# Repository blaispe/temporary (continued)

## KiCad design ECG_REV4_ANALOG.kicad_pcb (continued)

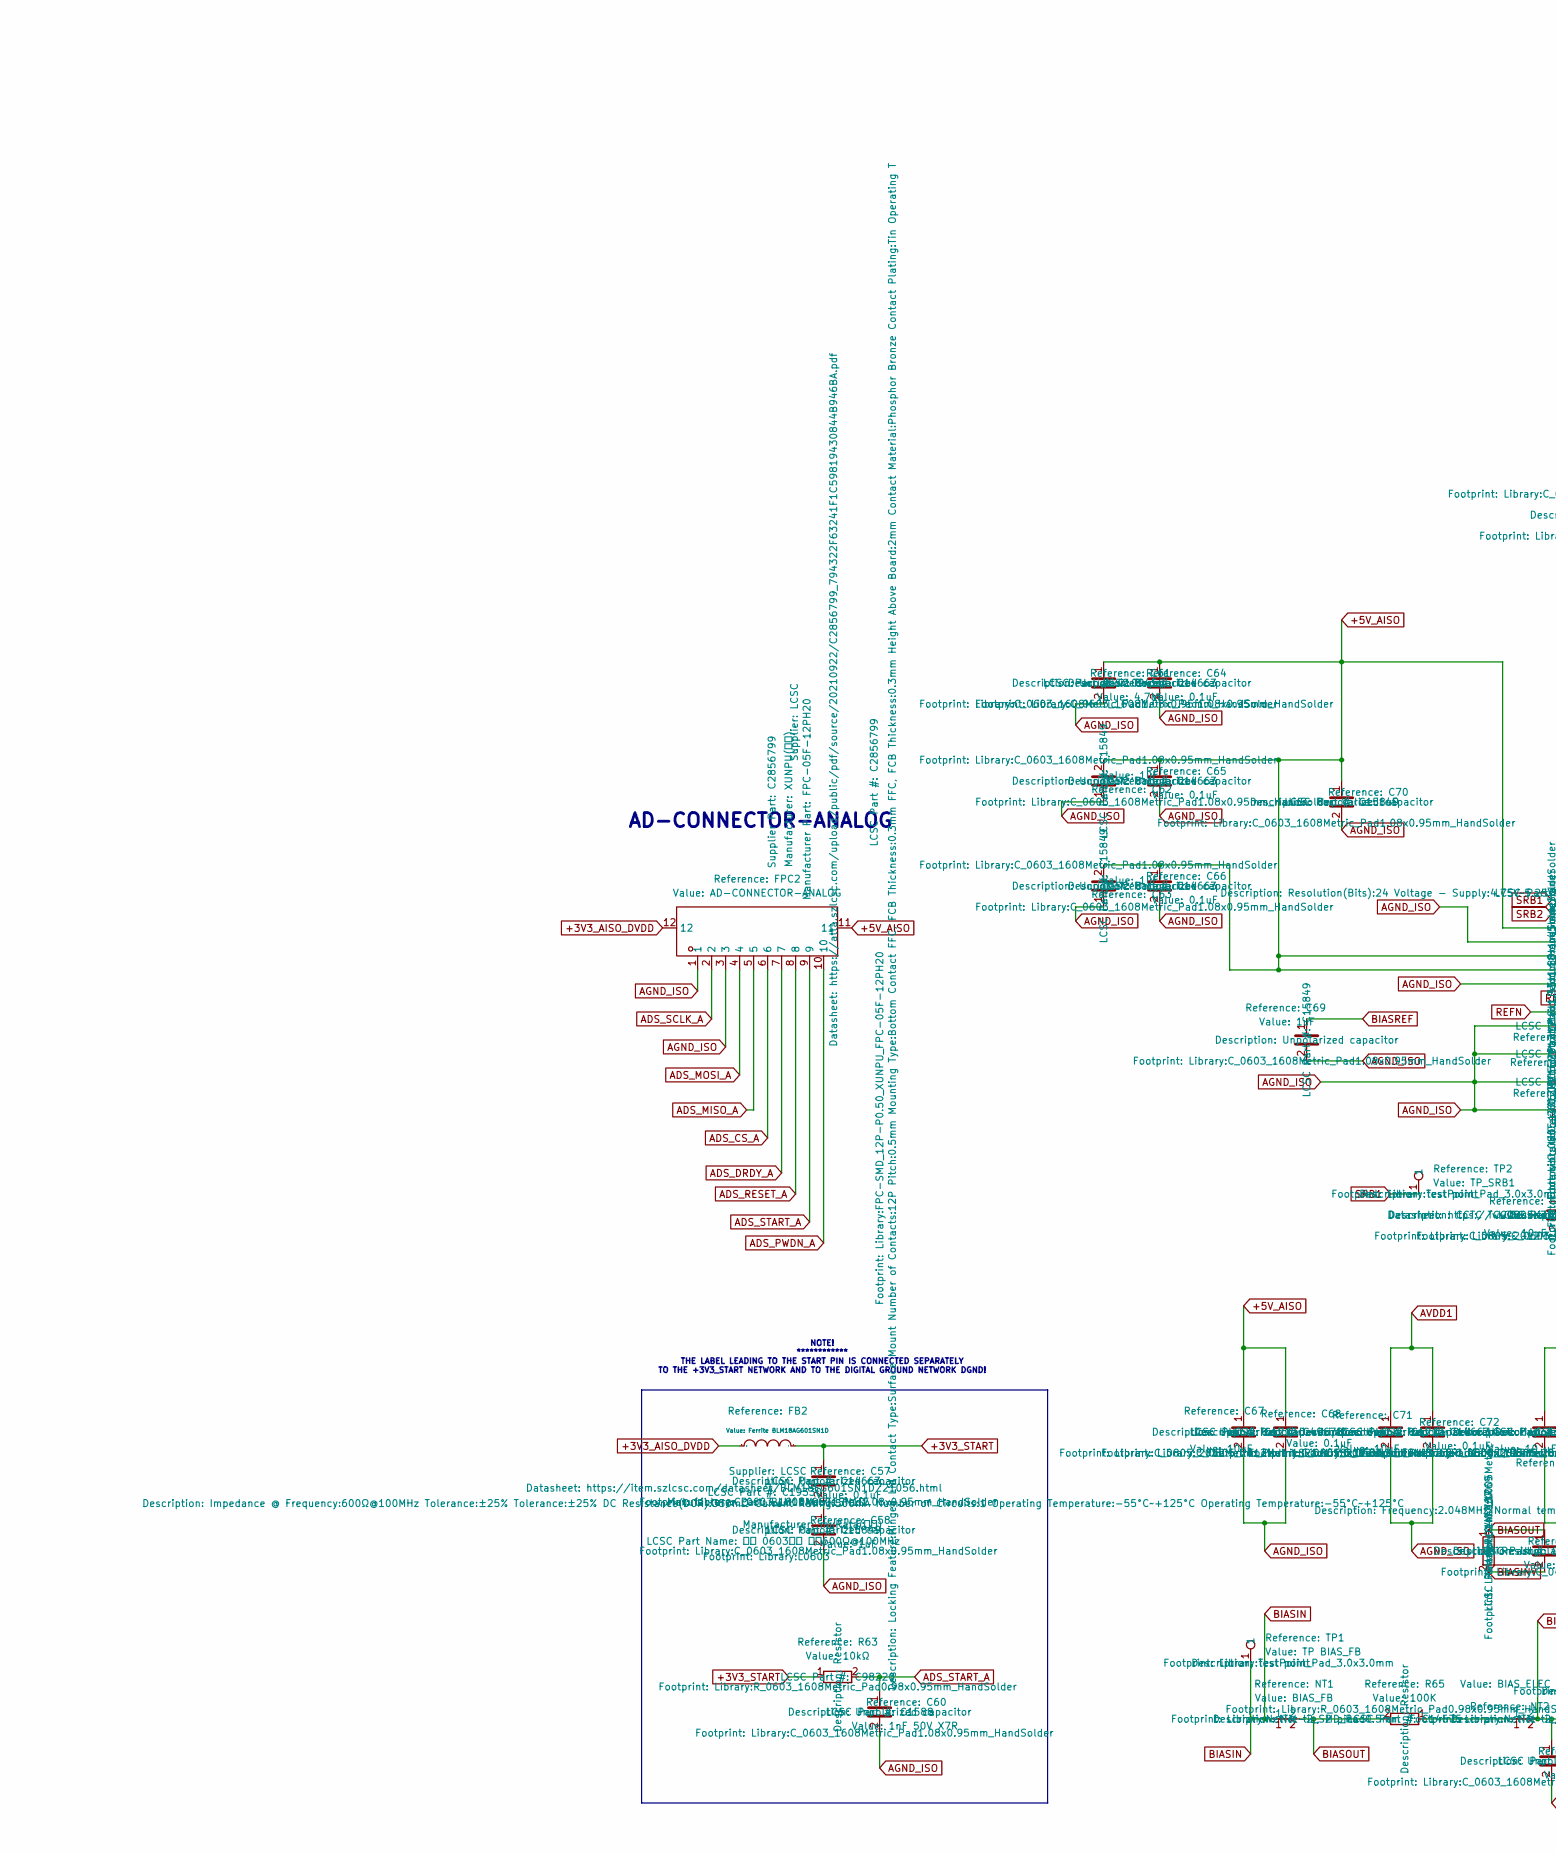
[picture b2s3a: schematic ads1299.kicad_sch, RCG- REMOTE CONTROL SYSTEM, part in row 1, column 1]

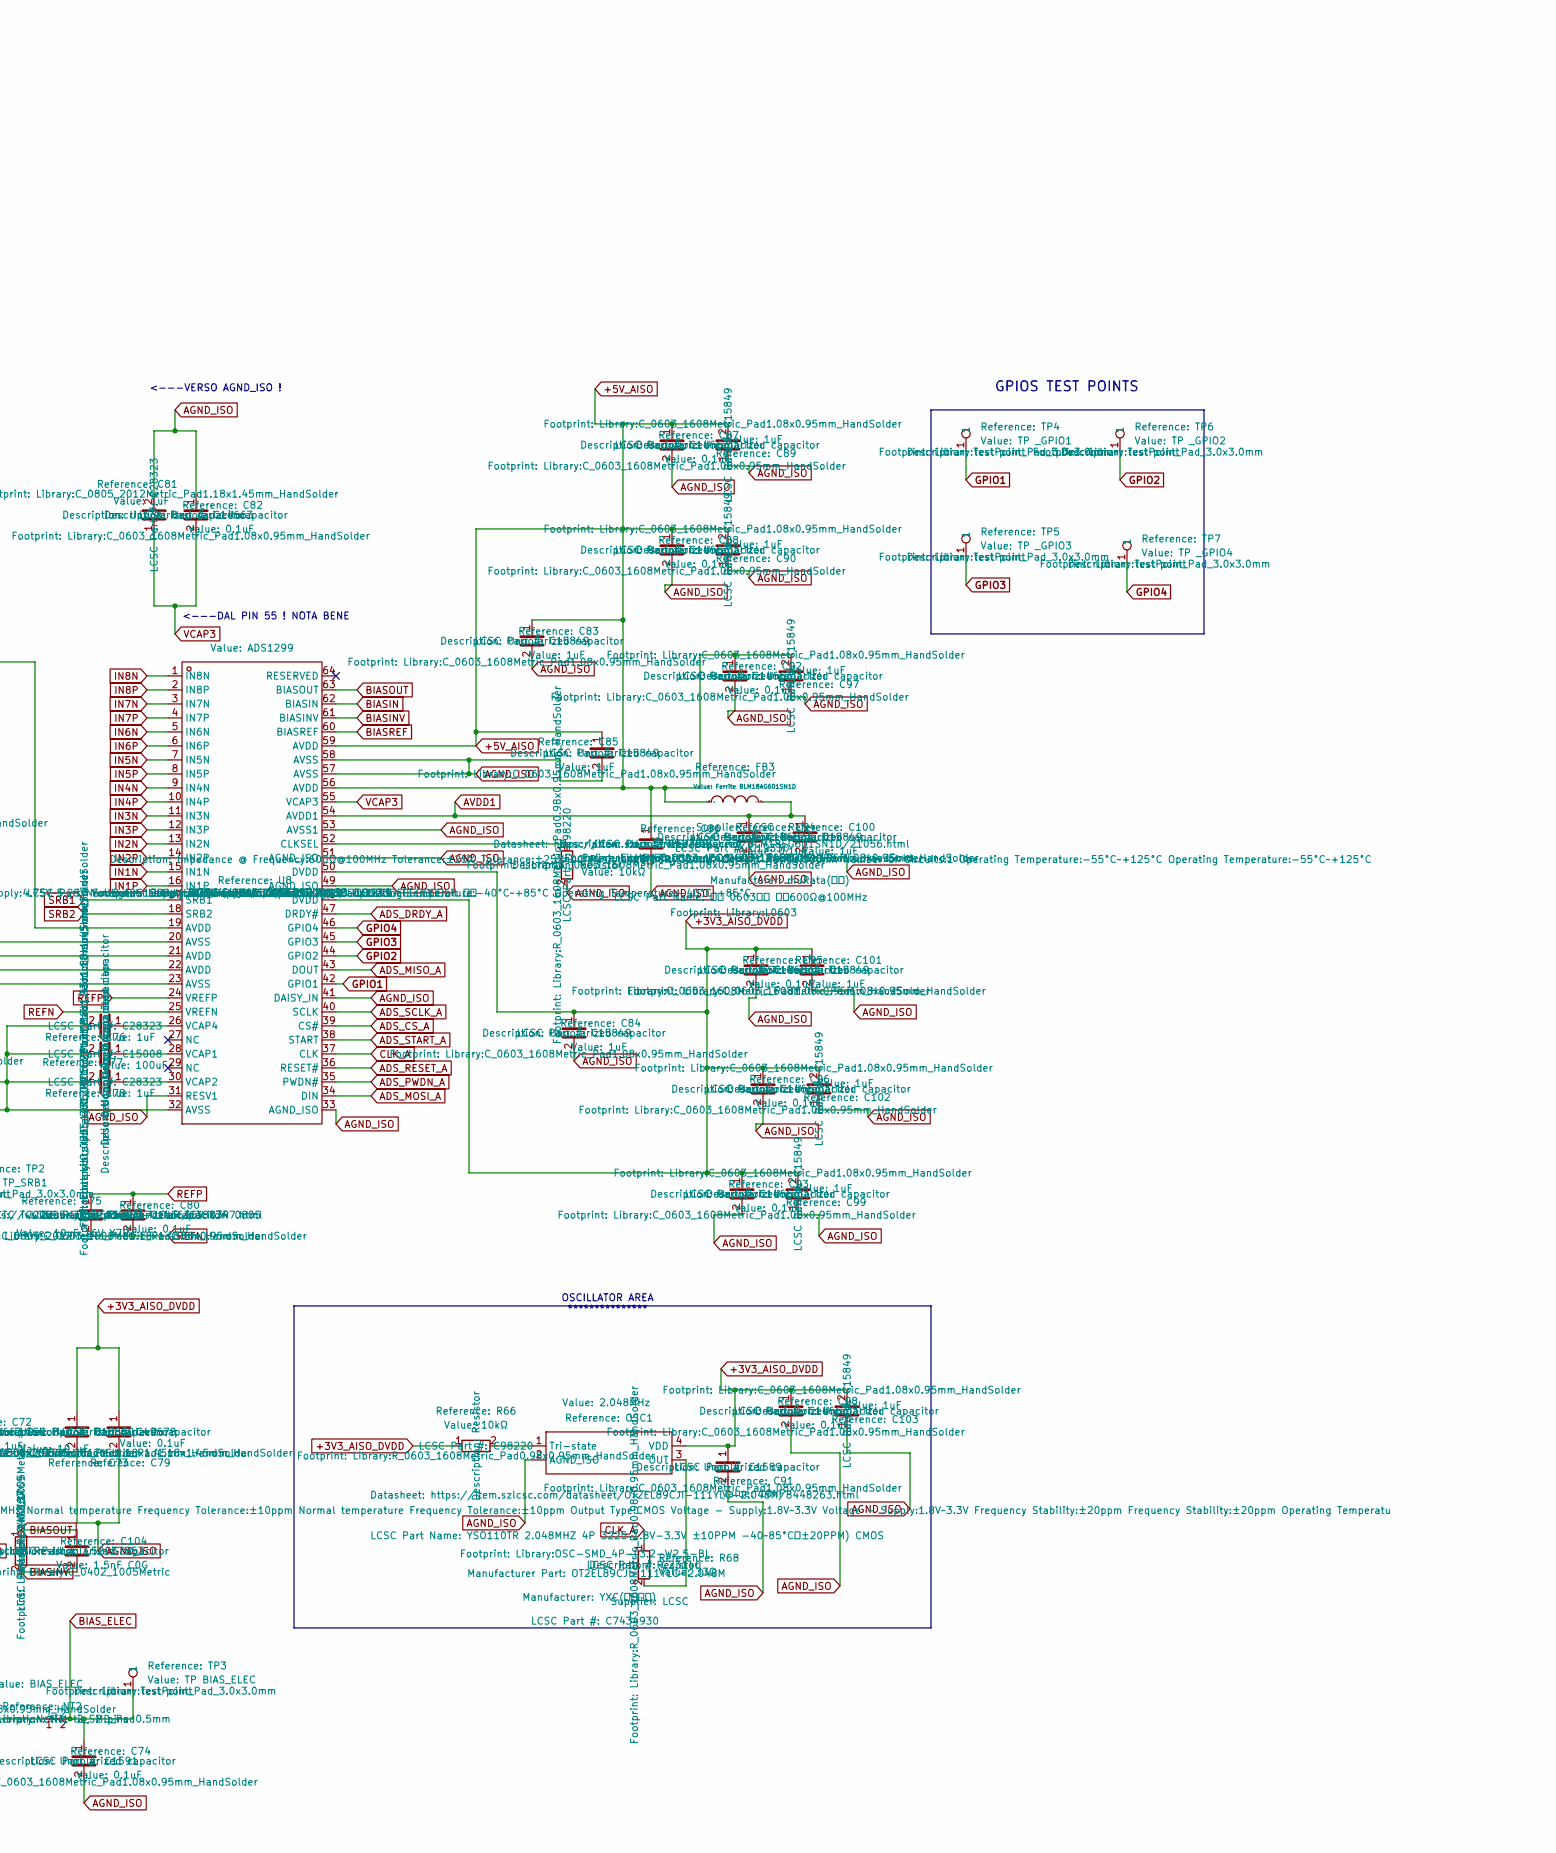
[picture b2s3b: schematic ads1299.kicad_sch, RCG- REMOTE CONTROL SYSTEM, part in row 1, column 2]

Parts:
C57, C64, C65, C66, C72, C80, C82, C87, C88, C92, C93, C94, C95, C96, C98: 0.1uF; C_0603_1608Metric_Pad1.08x0.95mm_HandSolder; LCSC Part # C14663
C58, C62, C63, C69, C70, C83, C84, C85, C89, C90, C97, C99, C100, C101, C102, C103: 1uF; C_0603_1608Metric_Pad1.08x0.95mm_HandSolder; LCSC Part # C15849
C60: 1nF 50V X7R; C_0603_1608Metric_Pad1.08x0.95mm_HandSolder; LCSC Part # C1588
C61: 4.7uf; C_0603_1608Metric_Pad1.08x0.95mm_HandSolder; LCSC Part # C109456
C67, C71: 10uF; C_0805_2012Metric_Pad1.18x1.45mm_HandSolder; LCSC Part # C1713
C68, C79: 0.1uF; C_0805_2012Metric_Pad1.18x1.45mm_HandSolder; LCSC Part # C49678
C73: 10 µF; C_0805_2012Metric_Pad1.18x1.45mm_HandSolder; LCSC Part # C15850
C74: 0.1uF; C_0603_1608Metric_Pad1.08x0.95mm_HandSolder; LCSC Part # C1591
C75: 10uF 16V X7R; C_0805_2012Metric_Pad1.18x1.45mm_HandSolder; LCSC Part # C380347
C76, C78, C81: 1uF; C_0805_2012Metric_Pad1.18x1.45mm_HandSolder; LCSC Part # C28323
C77: 100uF; C_1206_3216Metric_Pad1.33x1.80mm_HandSolder; LCSC Part # C15008
C86: 10uF; C_0603_1608Metric_Pad1.08x0.95mm_HandSolder; LCSC Part # C19702
C91: 10nF; C_0603_1608Metric_Pad1.08x0.95mm_HandSolder; LCSC Part # C1589
C104: 1.5nF C0G; C_0402_1005Metric; LCSC Part # C52037853
FB2, FB3: Ferrite BLM18AG601SN1D; L0603; Manufacturer Part BLM18AG601SN1D; LCSC Part # C19330
FPC2: AD-CONNECTOR-ANALOG; FPC-SMD_12P-P0.50_XUNPU_FPC-05F-12PH20; Manufacturer Part FPC-05F-12PH20; LCSC Part # C2856799
NT1: BIAS_FB; NetTie-2_SMD_Pad0.5mm
NT2: BIAS_ELEC; NetTie-2_SMD_Pad0.5mm
OSC1: 2.048MHz; OSC-SMD_4P-L3.2-W2.5-BL; Manufacturer Part OT2EL89CJI-111YLC-2.048M; LCSC Part # C7434930
R63, R66, R67: 10kΩ; R_0603_1608Metric_Pad0.98x0.95mm_HandSolder; LCSC Part # C98220
R65: 100K; R_0603_1608Metric_Pad0.98x0.95mm_HandSolder; LCSC Part # C14675
R68: 33Ω; R_0603_1608Metric_Pad0.98x0.95mm_HandSolder; LCSC Part # C23140
R69: 1M 1%; R_0402_1005Metric; LCSC Part # C144787
TP1: TP BIAS_FB; TestPoint_Pad_3.0x3.0mm
TP2: TP_SRB1; TestPoint_Pad_3.0x3.0mm
TP3: TP BIAS_ELEC; TestPoint_Pad_3.0x3.0mm
TP4: TP _GPIO1; TestPoint_Pad_3.0x3.0mm
TP5: TP _GPIO3; TestPoint_Pad_3.0x3.0mm
TP6: TP _GPIO2; TestPoint_Pad_3.0x3.0mm
TP7: TP _GPIO4; TestPoint_Pad_3.0x3.0mm
U8: ADS1299; TQFP-64_L10.0-W10.0-P0.50-LS12.0-TL; Manufacturer Part ADS1299IPAGR; LCSC Part # C476817

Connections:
+3V3_AISO_DVDD: C73.1, C79.1, C84.1, C91.1, C93.1, C95.1, C96.1, C98.1, C99.2, C101.1, C102.2, C103.2, FB2.1, FPC2.12, OSC1.4 (VDD), R66.1, U8.48 (DVDD), U8.50 (DVDD)
+3V3_START: C57.1, FB2.2, R63.1
+5V_AISO: C61.1, C62.2, C63.2, C64.1, C65.1, C66.1, C67.1, C68.1, C70.1, C83.1, C85.1, C86.1, C87.1, C88.1, C89.2, C90.2, C92.1, C97.2, FB3.1, FPC2.11, U8.19 (AVDD), U8.21 (AVDD), U8.22 (AVDD), U8.56 (AVDD), U8.59 (AVDD)
ADS_CS_A: FPC2.6, U8.39 (CS#)
ADS_DRDY_A: FPC2.7, U8.47 (DRDY#)
ADS_MISO_A: FPC2.5, U8.43 (DOUT)
ADS_MOSI_A: FPC2.4, U8.34 (DIN)
ADS_PWDN_A: FPC2.10, U8.35 (PWDN#)
ADS_RESET_A: FPC2.8, U8.36 (RESET#)
ADS_SCLK_A: FPC2.2, U8.40 (SCLK)
ADS_START_A: C60.1, FPC2.9, R63.2, U8.38 (START)
AGND_ISO: C58.2, C60.2, C61.2, C62.1, C63.1, C64.2, C65.2, C66.2, C67.2, C68.2, C69.2, C70.2, C71.2, C72.2, C73.2, C74.2, C76.2, C77.2, C78.2, C79.2, C81.2, C82.1, C83.2, C84.2, C85.2, C86.2, C87.2, C88.2, C89.1, C90.1, C91.2, C92.2, C93.2, C94.2, C95.2, C96.2, C97.1, C98.2, C99.1, C100.2, C101.2, C102.1, C103.1, FPC2.1, FPC2.3, OSC1.2 (AGND_ISO), R67.2, U8.20 (AVSS), U8.23 (AVSS), U8.31 (RESV1), U8.32 (AVSS), U8.33 (AGND_ISO), U8.41 (DAISY_IN), U8.49 (AGND_ISO), U8.51 (AGND_ISO), U8.53 (AVSS1), U8.57 (AVSS), U8.58 (AVSS); also elsewhere on the board
AVDD1: C71.1, C72.1, C94.1, C100.1, FB3.2, U8.54 (AVDD1)
BIASIN: NT1.1, TP1.1 (1_1), U8.62 (BIASIN)
BIASINV: C104.2, R69.2, U8.61 (BIASINV)
BIASOUT: C104.1, NT1.2, R65.2, R69.1, U8.63 (BIASOUT)
BIASREF: C69.1, U8.60 (BIASREF); also elsewhere on the board
BIAS_ELEC: C74.1, NT2.2, TP3.1 (1_1); also elsewhere on the board
CLK_A: R68.1, U8.37 (CLK)
GPIO1: TP4.1 (1_1), U8.42 (GPIO1)
GPIO2: TP6.1 (1_1), U8.44 (GPIO2)
GPIO3: TP5.1 (1_1), U8.45 (GPIO3)
GPIO4: TP7.1 (1_1), U8.46 (GPIO4)
IN1N: U8.15 (IN1N); also elsewhere on the board
IN1P: U8.16 (IN1P); also elsewhere on the board
IN2N: U8.13 (IN2N); also elsewhere on the board
IN2P: U8.14 (IN2P); also elsewhere on the board
IN3N: U8.11 (IN3N); also elsewhere on the board
IN3P: U8.12 (IN3P); also elsewhere on the board
IN4N: U8.9 (IN4N); also elsewhere on the board
IN4P: U8.10 (IN4P); also elsewhere on the board
IN5N: U8.7 (IN5N); also elsewhere on the board
IN5P: U8.8 (IN5P); also elsewhere on the board
IN6N: U8.5 (IN6N); also elsewhere on the board
IN6P: U8.6 (IN6P); also elsewhere on the board
IN7N: U8.3 (IN7N); also elsewhere on the board
IN7P: U8.4 (IN7P); also elsewhere on the board
IN8N: U8.1 (IN8N); also elsewhere on the board
IN8P: U8.2 (IN8P); also elsewhere on the board
unnamed: C57.2, C58.1
unnamed: NT2.1, R65.1
unnamed: OSC1.3 (OUT), R68.2
unnamed: OSC1.1 (Tri-state), R66.2
unnamed: R67.1, U8.52 (CLKSEL)
unnamed: C77.1, U8.28 (VCAP1)
unnamed: C78.1, U8.30 (VCAP2)
unnamed: C76.1, U8.26 (VCAP4)
REFN: C75.2, C80.2, U8.25 (VREFN)
REFP: C75.1, C80.1, U8.24 (VREFP)
SRB1: TP2.1 (1_1), U8.17 (SRB1)
SRB2: U8.18 (SRB2); also elsewhere on the board
VCAP3: C81.1, C82.2, U8.55 (VCAP3)

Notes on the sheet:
<---VERSO AGND_ISO !
AD-CONNECTOR-ANALOG
OSCILLATOR AREA ***************
<---DAL PIN 55 ! NOTA BENE
NOTE! ************ THE LABEL LEADING TO THE START PIN IS CONNECTED SEPARATELY TO THE +3V3_START NETWORK AND TO THE DIGITAL GROUND NETWORK DGND!
GPIOS TEST POINTS

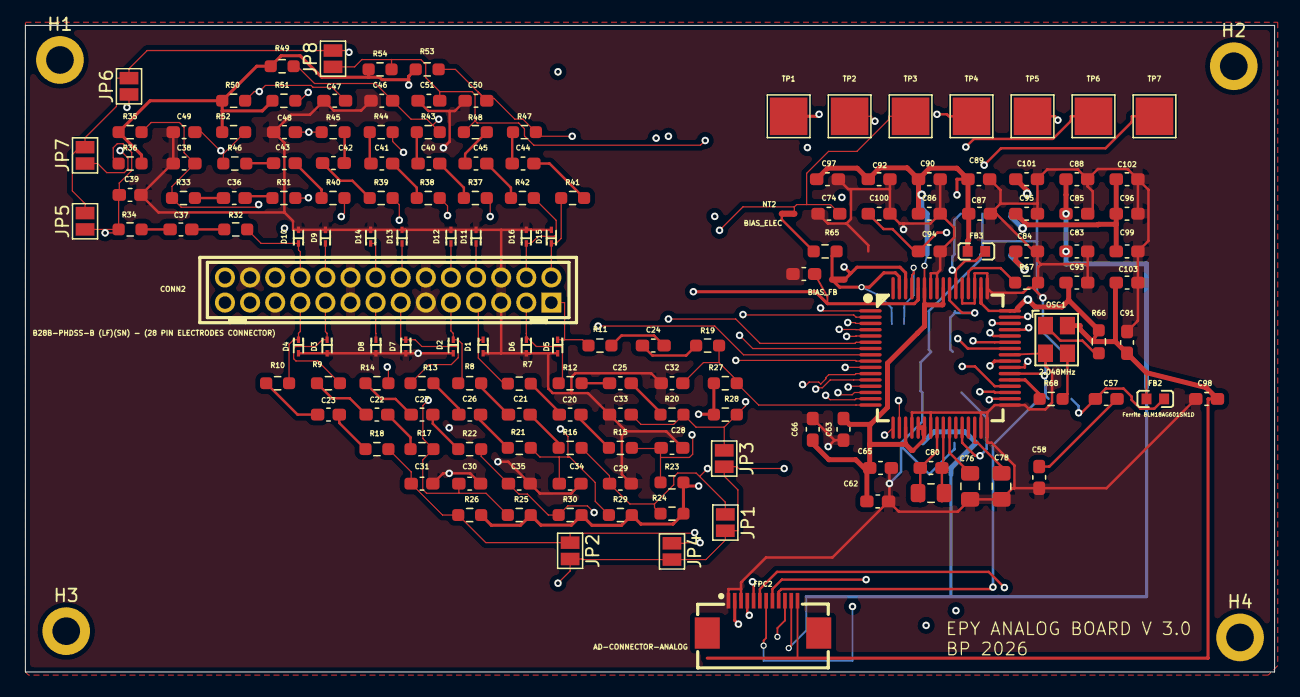
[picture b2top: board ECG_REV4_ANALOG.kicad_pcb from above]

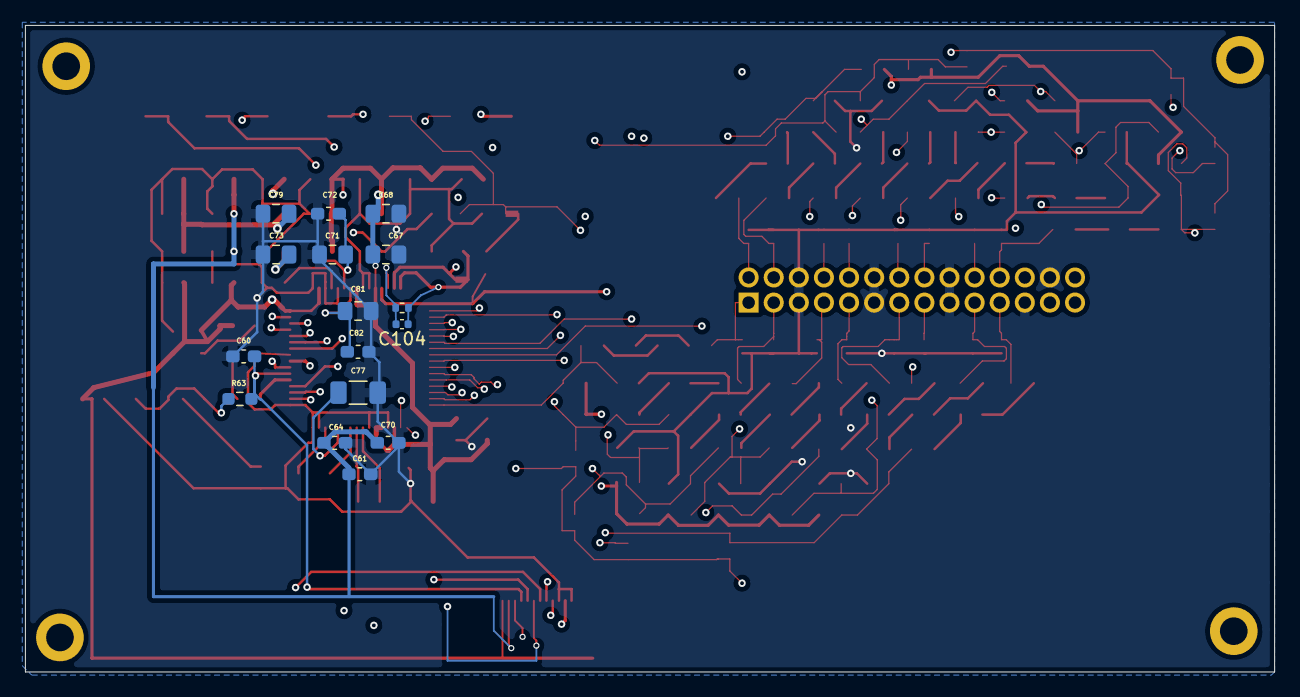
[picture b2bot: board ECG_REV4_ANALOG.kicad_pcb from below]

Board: 4 copper layers, 99.5 x 51.5 mm, 176 parts (16 on the bottom side), 101 nets.

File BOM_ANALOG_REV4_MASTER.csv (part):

"Reference","Value","Footprint","Quantity","DNP","Manufacturer","Manufacturer Part","MP","LCSC","Datasheet","Description"
"C20","1uF","Library:C_0603_1608Metric_Pad1.08x0.95mm_HandSolder","1","","","","","C15849","","Unpolarized capacitor"
"C21","1uF","Library:C_0603_1608Metric_Pad1.08x0.95mm_HandSolder","1","","","","","C15849","","Unpolarized capacitor"
"C22","1uF","Library:C_0603_1608Metric_Pad1.08x0.95mm_HandSolder","1","","","","","C15849","","Unpolarized capacitor"
"C23","1uF","Library:C_0603_1608Metric_Pad1.08x0.95mm_HandSolder","1","","","","","C15849","","Unpolarized capacitor"
"C24","1uF","Library:C_0603_1608Metric_Pad1.08x0.95mm_HandSolder","1","","","","","C15849","","Unpolarized capacitor"
"C25","1uF","Library:C_0603_1608Metric_Pad1.08x0.95mm_HandSolder","1","","","","","C15849","","Unpolarized capacitor"
"C26","1uF","Library:C_0603_1608Metric_Pad1.08x0.95mm_HandSolder","1","","","","","C15849","","Unpolarized capacitor"
"C27","1uF","Library:C_0603_1608Metric_Pad1.08x0.95mm_HandSolder","1","","","","","C15849","","Unpolarized capacitor"
"C28","220pF","Library:C_0603_1608Metric_Pad1.08x0.95mm_HandSolder","1","","","","","C1603","","Unpolarized capacitor"
"C29","220pF","Library:C_0603_1608Metric_Pad1.08x0.95mm_HandSolder","1","","","","","C1603","","Unpolarized capacitor"
"C30","220pF","Library:C_0603_1608Metric_Pad1.08x0.95mm_HandSolder","1","","","","","C1603","","Unpolarized capacitor"
"C31","220pF","Library:C_0603_1608Metric_Pad1.08x0.95mm_HandSolder","1","","","","","C1603","","Unpolarized capacitor"
"C32","220pF","Library:C_0603_1608Metric_Pad1.08x0.95mm_HandSolder","1","","","","","C1603","","Unpolarized capacitor"
"C33","220pF","Library:C_0603_1608Metric_Pad1.08x0.95mm_HandSolder","1","","","","","C1603","","Unpolarized capacitor"
"C34","220pF","Library:C_0603_1608Metric_Pad1.08x0.95mm_HandSolder","1","","","","","C1603","","Unpolarized capacitor"
"C35","220pF","Library:C_0603_1608Metric_Pad1.08x0.95mm_HandSolder","1","","","","","C1603","","Unpolarized capacitor"
"C36","1uF","Library:C_0603_1608Metric_Pad1.08x0.95mm_HandSolder","1","","","","","C15849","","Unpolarized capacitor"
"C37","1uF","Library:C_0603_1608Metric_Pad1.08x0.95mm_HandSolder","1","","","","","C15849","","Unpolarized capacitor"
"C38","220pF","Library:C_0603_1608Metric_Pad1.08x0.95mm_HandSolder","1","","","","","C1603","","Unpolarized capacitor"
"C39","220pF","Library:C_0603_1608Metric_Pad1.08x0.95mm_HandSolder","1","","","","","C1603","","Unpolarized capacitor"
"C40","1uF","Library:C_0603_1608Metric_Pad1.08x0.95mm_HandSolder","1","","","","","C15849","","Unpolarized capacitor"
"C41","1uF","Library:C_0603_1608Metric_Pad1.08x0.95mm_HandSolder","1","","","","","C15849","","Unpolarized capacitor"
"C42","1uF","Library:C_0603_1608Metric_Pad1.08x0.95mm_HandSolder","1","","","","","C15849","","Unpolarized capacitor"
"C43","1uF","Library:C_0603_1608Metric_Pad1.08x0.95mm_HandSolder","1","","","","","C15849","","Unpolarized capacitor"
"C44","1uF","Library:C_0603_1608Metric_Pad1.08x0.95mm_HandSolder","1","","","","","C15849","","Unpolarized capacitor"
"C45","1uF","Library:C_0603_1608Metric_Pad1.08x0.95mm_HandSolder","1","","","","","C15849","","Unpolarized capacitor"
"C46","220pF","Library:C_0603_1608Metric_Pad1.08x0.95mm_HandSolder","1","","","","","C1603","","Unpolarized capacitor"
"C47","220pF","Library:C_0603_1608Metric_Pad1.08x0.95mm_HandSolder","1","","","","","C1603","","Unpolarized capacitor"
"C48","220pF","Library:C_0603_1608Metric_Pad1.08x0.95mm_HandSolder","1","","","","","C1603","","Unpolarized capacitor"
"C49","220pF","Library:C_0603_1608Metric_Pad1.08x0.95mm_HandSolder","1","","","","","C1603","","Unpolarized capacitor"
"C50","220pF","Library:C_0603_1608Metric_Pad1.08x0.95mm_HandSolder","1","","","","","C1603","","Unpolarized capacitor"
"C51","220pF","Library:C_0603_1608Metric_Pad1.08x0.95mm_HandSolder","1","","","","","C1603","","Unpolarized capacitor"
"C57","0.1uF","Library:C_0603_1608Metric_Pad1.08x0.95mm_HandSolder","1","","","","","C14663","","Unpolarized capacitor"
"C58","1uF","Library:C_0603_1608Metric_Pad1.08x0.95mm_HandSolder","1","","","","","C15849","","Unpolarized capacitor"
"C60","1nF 50V X7R","Library:C_0603_1608Metric_Pad1.08x0.95mm_HandSolder","1","","","","","C1588","","Unpolarized capacitor"
"C61","4.7uf","Library:C_0603_1608Metric_Pad1.08x0.95mm_HandSolder","1","","","","","C109456","","Unpolarized capacitor"
"C62","1uF","Library:C_0603_1608Metric_Pad1.08x0.95mm_HandSolder","1","","","","","C15849","","Unpolarized capacitor"
"C63","1uF","Library:C_0603_1608Metric_Pad1.08x0.95mm_HandSolder","1","","","","","C15849","","Unpolarized capacitor"
"C64","0.1uF","Library:C_0603_1608Metric_Pad1.08x0.95mm_HandSolder","1","","","","","C14663","","Unpolarized capacitor"
"C65","0.1uF","Library:C_0603_1608Metric_Pad1.08x0.95mm_HandSolder","1","","","","","C14663","","Unpolarized capacitor"
"C66","0.1uF","Library:C_0603_1608Metric_Pad1.08x0.95mm_HandSolder","1","","","","","C14663","","Unpolarized capacitor"
"C67","10uF","Library:C_0805_2012Metric_Pad1.18x1.45mm_HandSolder","1","","","","","C1713","","Unpolarized capacitor"
"C68","0.1uF","Library:C_0805_2012Metric_Pad1.18x1.45mm_HandSolder","1","","","","","C49678","","Unpolarized capacitor"
"C69","1uF","Library:C_0603_1608Metric_Pad1.08x0.95mm_HandSolder","1","","","","","C15849","","Unpolarized capacitor"
"C70","1uF","Library:C_0603_1608Metric_Pad1.08x0.95mm_HandSolder","1","","","","","C15849","","Unpolarized capacitor"
"C71","10uF","Library:C_0805_2012Metric_Pad1.18x1.45mm_HandSolder","1","","","","","C1713","","Unpolarized capacitor"
"C72","0.1uF","Library:C_0603_1608Metric_Pad1.08x0.95mm_HandSolder","1","","","","","C14663","","Unpolarized capacitor"
"C73","10 µF","Library:C_0805_2012Metric_Pad1.18x1.45mm_HandSolder","1","","","","","C15850","","Unpolarized capacitor"
"C74","0.1uF","Library:C_0603_1608Metric_Pad1.08x0.95mm_HandSolder","1","","","","","C1591","","Unpolarized capacitor"
"C75","10uF 16V X7R","Library:C_0805_2012Metric_Pad1.18x1.45mm_HandSolder","1","","","","","C380347","https://www.lcsc.com/product-detail/C380347.html","CCTC TCC0805X7R106K160FT, 10uF 16V X7R 0805"
"C76","1uF","Library:C_0805_2012Metric_Pad1.18x1.45mm_HandSolder","1","","","","","C28323","","Unpolarized capacitor"
"C77","100uF","Library:C_1206_3216Metric_Pad1.33x1.80mm_HandSolder","1","","","","","C15008","","Unpolarized capacitor"
"C78","1uF","Library:C_0805_2012Metric_Pad1.18x1.45mm_HandSolder","1","","","","","C28323","","Unpolarized capacitor"
"C79","0.1uF","Library:C_0805_2012Metric_Pad1.18x1.45mm_HandSolder","1","","","","","C49678","","Unpolarized capacitor"
"C80","0.1uF","Library:C_0603_1608Metric_Pad1.08x0.95mm_HandSolder","1","","","","","C14663","","Unpolarized capacitor"
"C81","1uF","Library:C_0805_2012Metric_Pad1.18x1.45mm_HandSolder","1","","","","","C28323","","Unpolarized capacitor"
"C82","0.1uF","Library:C_0603_1608Metric_Pad1.08x0.95mm_HandSolder","1","","","","","C14663","","Unpolarized capacitor"
"C83","1uF","Library:C_0603_1608Metric_Pad1.08x0.95mm_HandSolder","1","","","","","C15849","","Unpolarized capacitor"
"C84","1uF","Library:C_0603_1608Metric_Pad1.08x0.95mm_HandSolder","1","","","","","C15849","","Unpolarized capacitor"
"C85","1uF","Library:C_0603_1608Metric_Pad1.08x0.95mm_HandSolder","1","","","","","C15849","","Unpolarized capacitor"
"C86","10uF","Library:C_0603_1608Metric_Pad1.08x0.95mm_HandSolder","1","","","","","C19702","","Unpolarized capacitor"
"C87","0.1uF","Library:C_0603_1608Metric_Pad1.08x0.95mm_HandSolder","1","","","","","C14663","","Unpolarized capacitor"
"C88","0.1uF","Library:C_0603_1608Metric_Pad1.08x0.95mm_HandSolder","1","","","","","C14663","","Unpolarized capacitor"
"C89","1uF","Library:C_0603_1608Metric_Pad1.08x0.95mm_HandSolder","1","","","","","C15849","","Unpolarized capacitor"
"C90","1uF","Library:C_0603_1608Metric_Pad1.08x0.95mm_HandSolder","1","","","","","C15849","","Unpolarized capacitor"
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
